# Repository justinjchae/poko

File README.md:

<div align="center">

# Poko

**A palm-sized, phone-free companion: the things you'd pick up your phone for, without picking up your phone.**

A round 240×240 display, one rotating ring, a haptic motor, a microphone and BLE to an iPhone app.
It snaps onto the back of the phone like a MagSafe accessory, or comes off and stands in for the phone at the gym, the library or on a walk.

`nRF52840` · `Zephyr / nRF Connect SDK` · `LVGL` · `BLE` · `MCUboot OTA` · `SwiftUI` · `Fusion 360 API` · `KiCad` · `JLCPCB`

<br>

&nbsp;

<sub>Left: the V1B prototype in hand, home ring on Voice Memos. Right: Pomodoro → workout logging → recording and browsing memos → Now Playing, all from the thumb wheel (2× speed).</sub>

</div>

---

## Contents

- [What it does](#what-it-does)
- [Requirements I've locked](#requirements-ive-locked)
- [System architecture](#system-architecture)
- [Hardware](#hardware)
- [Firmware](#firmware)
- [iPhone companion app](#iphone-companion-app)
- [Measured results](#measured-results)
- [Design direction](#design-direction)
- [Where it came from: Pokodoro (v0)](#where-it-came-from-pokodoro-v0)
- [Status and roadmap](#status-and-roadmap)
- [Repo map](#repo-map)
- [How this was built](#how-this-was-built)

---

## What it does

| | Use case | On the device | On the phone |
|---|---|---|---|
| ⏱ | **Pomodoro focus timer** | Ring sets the time, haptic ticks while turning, glanceable progress ring, silent vibration at the end | none |
| 🏋️ | **Workout tracker** | Today's exercises, the weight prefilled from last time with plates per side, rest timer, every set saved to flash | Routines are edited in the app and synced |
| 🎙 | **Voice memos** | Hold to record from any screen; ADPCM to on-board flash; works offline | Pulled over BLE, transcribed, titled and routed to Reminders, groceries or Calendar |
| 🎵 | Now Playing *(extra)* | Play/pause/skip and 16-step volume over Apple Media Service | none |
| ⌨️ | Desk keyboard *(extra)* | USB/BLE HID: ring as a scroll wheel, voice-to-typing | Transcription |

**What it won't do:** show notifications, run feeds, or ask you to scroll. One hand, eyes-free, every action confirmed by vibration.

---

## Requirements I've locked

These are the constraints every hardware and firmware decision is checked against. Full reasoning is in [`SPEC.md`](SPEC.md) and the part-by-part tracker [`docs/hardware/LOCK.md`](docs/hardware/LOCK.md).

### Product

| Requirement | Target |
|---|---|
| Form factor | MagSafe-style accessory, 60 × 90 mm outline, half-round top |
| Thickness | **8–9 mm** for production (the printed prototype is 18.8 mm; this is the hardest constraint) |
| Interaction | One hand, eyes-free. Turn moves focus, click commits; turning never silently changes a value |
| Navigation depth | Home → app → one detail level, max. Apps live at fixed clock positions on the home ring |
| Battery | Lasts a normal day; ~0.5 mA sleep-floor target |
| Offline | Device works without the phone; the phone does the heavy lifting (transcription, sync) |
| Manufacturing | Every part sourceable at ~100 units, JLC-assemblable, no injection mold for the first run |
| Prototyping rule | Internals must be printable (PLA/TPU) or stock commodity parts; dimensions tunable by reprint |
| Access rule | Every prototype breaks out spare GPIOs, 3V3/GND and an outside-reachable reset |

### Hardware decisions

| Subsystem | Decision | Why |
|---|---|---|
| MCU | **nRF52840**: XIAO Sense on a carrier board for the first batch, Raytac MDBT50Q module for production | BLE + battery life over the ESP32-S3 used in v0; the module is ~1.5–3 mm thinner and ~$6 cheaper than soldering down a dev board |
| Display | **1.28" round GC9A01 TFT**, 240×240, 4-wire SPI, bare 16-pin FPC panel | Round AMOLED was RFQ-only with ~1,000 MOQ; TFT has transparent low-volume pricing. Cost: the backlight dominates power, so it gets a discrete constant-current sink with PWM |
| Input | **Rotating ring + mechanical select**, AS5600 magnetic angle sensor on-axis | EC11 encoders are too thick for 8 mm. Optical, magnetic strip, inductive PCB coil and capacitive were weighed, and the press-sensing options were tested on rigs (see [Hardware](#hardware)) |
| Haptics | **LRA + DRV2605L**; detents simulated in software | One actuator gives detents, clicks and alerts with no mechanical detent to wear out or add thickness |
| Power | 500 mAh 303450 LiPo (3.0 mm thick), single-cell linear charger | Chosen to protect the thickness budget; battery life comes from backlight PWM and a low sleep floor |
| Storage | 16 MB QSPI NOR flash on the production board (memos + OTA slot), no SD card | About 31 minutes of memos alongside a full OTA image |
| Firmware | **Zephyr / nRF Connect SDK** | Real power management, MCUboot signed OTA, BLE stack. Arduino and CircuitPython were used only for bring-up |
| Enclosure | Machined shell (quote pending) with 3D-printed internals | Small batch; no mold until demand is proven |

---

## System architecture

```mermaid
flowchart LR
    subgraph Device["Poko (nRF52840, Zephyr)"]
        Ring["Ring<br/>AS5600 / EC11"] --> Input["Input + detent engine"]
        Btn["Select button"] --> Input
        IMU["6-axis IMU"] --> Pickup["Pickup-to-wake<br/>auto-rotate"]
        Mic["PDM mic"] --> Rec["Recorder<br/>ADPCM"]
        Input --> Shell["App shell<br/>home ring + apps"]
        Pickup --> Shell
        Shell --> UI["LVGL UI"] --> LCD["GC9A01 240×240"]
        Shell --> Haptic["Haptic patterns"] --> LRA["DRV2605L + LRA"]
        Rec --> Flash["Flash<br/>memo store"]
        Shell --> BLE["BLE<br/>GATT · AMS · HID · SMP"]
        Flash --> BLE
        OTA["MCUboot<br/>signed OTA"] -.-> Flash
    end

    subgraph Phone["iPhone companion (SwiftUI)"]
        Sync["Memo sync"] --> STT["On-device<br/>transcription"]
        STT --> Route["Voice-action router"]
        Route --> Rem["Reminders /<br/>groceries"]
        Route --> Cal["Google Calendar"]
        Routines["Workout routines"]
    end

    BLE <--> Sync
    BLE <--> Routines
```

---

## Hardware

### Prototype progression

| Stage | What | Status |
|---|---|---|
| **Breadboard bring-up** | XIAO nRF52840 Sense + round GC9A01 module + EC11 encoder (detent removed, shaft cut down) + ERM motor. CircuitPython first, then Zephyr | Done (Sept 2026) |
| **Enclosure V1B** | Two-part printed shell, 33 mm thumb wheel, display retainer, VHB-mounted XIAO, magnet in the back cover, support-free print orientations. 18.8 mm thick | Printed, carried daily to the gym and library |
| **Enclosure V2 (inset)** | Parametric Fusion 360 model driven from Python ([`cad/enclosure_v2_inset.py`](cad/enclosure_v2_inset.py)): 8 mm stack, datum-based [tolerance stack](docs/hardware/tolerance-stack.md), pairwise interference checks | Modelled |
| **Knob and ring test rigs** | Printed rigs + an ESP32-S3 logger streaming AS5600 angle/AGC/magnitude at 100 Hz to a Web Serial visualizer | Built and tested, see below |
| **XIAO carrier PCB** | Chin board carrying the display FPC, AS5600, DRV2605L/LRA, backlight sink, select-switch footprints | Next: floorplan → schematic → JLC order |

<table>
<tr>
<td align="center"><br><sub>V1B opened: cell, wiring, magnet in the back cover</sub></td>
<td align="center"><br><sub>Breadboard bring-up</sub></td>
<td align="center"><br><sub>Protoboard for the first enclosure</sub></td>
<td align="center"><br><sub>EC11 opened to remove the detent spring</sub></td>
<td align="center"><br><sub>Cutting the encoder shaft down</sub></td>
</tr>
</table>

### Ring input: what the rigs showed

The ring has to feel premium (the iPod click wheel is the reference) inside an 8 mm stack, so I built rigs and measured before committing:

- **Friction roller → AS5600:** worked, but felt overcomplicated and thin. Set aside.
- **Whole-knob press detected from magnet field strength (AS5600 AGC):** at a ~1 mm gap, rest AGC was 68–76 and a centre press dropped it to 32–37. A detector ("AGC drops ≥ 25 below the 3 s peak, held 150 ms, rotation < 4°") replayed 3/3 centre presses, 3/3 edge presses and 0 false triggers on turns.
- **Trackpad-style ring (≈0.05 mm travel, printed cantilever springs, 45° flare retention):** the thumb's grip while only rotating (AGC 24–35) overlapped edge presses (25–29). One sensor couldn't separate them reliably.
- **Decision:** AS5600 on-axis for rotation + a thin mechanical tact switch for select, with three switch footprints and spare I2C/GPIO on the carrier so the mechanism can change without a board respin.

Scripts: [`cad/as5600_knob_rig.py`](cad/as5600_knob_rig.py), [`cad/ring_rig.py`](cad/ring_rig.py), [`firmware/tools/as5600_rig/`](firmware/tools/as5600_rig) (logger firmware + visualizer).

### Electrical design notes

- **Backlight sink:** AO3400A + TLV9001 constant-current loop, 2.2 Ω sense, PWM-derived reference, op-amp powered from a GPIO so it draws nothing in sleep, gate pull-down for the unpowered state.
- **Charger swap check:** MCP73831 → TP4054. The check caught that the MCP73831's STAT pin drives ~4.6 V into a 3.0 V GPIO, and that the TP4054 PROG formula changes above 150 mA. Details in [`docs/hardware/LOCK.md`](docs/hardware/LOCK.md).
- **Pin budget:** all 11 XIAO pads allocated (SPI display, shared I2C for AS5600 + DRV2605L, select, backlight PWM/enable), one spare, with solder jumpers for optional lines ([`docs/hardware/pins.md`](docs/hardware/pins.md)).
- **Supply chain:** JLC quoted the Raytac module at **$15.69** vs. its own $7.73 list price and $6.50–7.13 at TME. At 100 units that gap is ~$840, so volume orders point to sourcing it elsewhere. Assembly-tier costs are in [`docs/hardware/jlc-cost.md`](docs/hardware/jlc-cost.md).

---

## Firmware

A Zephyr application split into a small OS layer and apps (source in a private repo; happy to walk through it):

- **`os/`**: input (EC11 Gray-code decoder, AS5600 driver), detent and haptic engine, LVGL screen and widgets, power states (dim, sleep, pickup-to-wake from the IMU), battery ADC, PDM capture with ADPCM, NVS-backed memo store, BLE link (custom GATT, Apple Media Service, HID keyboard), USB HID, MCUboot OTA, crash capture.
- **`apps/`**: Pomodoro, Gym (with synced routines), Voice memos, Now Playing, Desk keyboard, Settings.
- **Tooling:** a bench build that measures frame time, a power-test app for current measurements, a memo-pull script, and a desktop LVGL simulator.

Each feature was specced as a numbered brief with acceptance criteria and an outcome write-up.

---

## iPhone companion app

SwiftUI app (XcodeGen project, source in the same private repo): memo sync over BLE, on-device transcription, automatic titles, a voice-action router (to-dos, groceries, Google Calendar via OAuth PKCE), and workout routine editing. A routing eval harness scores the router against synthetic and real memo sets.

---

## Measured results

| What | Result | How |
|---|---|---|
| Current, screen off / on / recording | 37.5 / 42.6 / 44.0 mA | Multimeter in series with the battery, USB unplugged ([`power.md`](docs/hardware/power.md)) |
| Backlight share of screen-on draw | 33.5 mA (~79%) | Voltage across the module's 8.2 Ω backlight resistor. This is why the production board gets a PWM current sink |
| OTA over BLE | 561 KB in ~34 s, 42.5 s swap | MCUboot. A battery pull mid-swap recovered, and all 105 stored memos kept matching CRCs ([`ota-checks.md`](docs/hardware/ota-checks.md)) |
| Boot time | 53 s → **4.4 s** | Traced to a per-key NVS walk at boot, replaced with a single pass |
| Voice-to-text, release to typed | 5.9–6.3 s → ~3.0–3.7 s | Timing marks on device and phone, 5–7 s utterances |
| Voice-action routing accuracy | 47/54 → **52/54** on real memos | Eval harness, Apple on-device model |
| Album-art decode | 65 ms avg / 167 ms max | Measured, then cut: it made the UI lag |

---

## Design direction

<table>
<tr>
<td width="45%"></td>
<td>

**Inspiration:** concentric orbits on black, like the iOS Solar System lock screen. They map naturally onto a round display and a ring you turn.

- Black background, thin white line art, **one accent colour**
- Thick arc progress rings for timers
- Apps sit at fixed clock positions; only the focus moves, so you can go straight to one ("gym is at 2")
- Cheap pixels: small objects move over static, rotationally symmetric backgrounds, with no full-screen redraws
- Every turn and click confirmed by haptics, so it works without looking

</td>
</tr>
</table>

---

## Where it came from: Pokodoro (v0)

Poko is the second version of a device I started in 2024: **Pokodoro**, a portable Pomodoro timer that tells you a session is over with a vibration instead of a beep, so it works in a library or an office. I sketched it, prototyped it on protoboard, laid out a 4-layer board in KiCad, had it fabricated, hand-soldered it and designed the enclosure.

<table>
<tr>
<td align="center"><br><sub>Assembled v0</sub></td>
<td align="center"><br><sub>Custom PCB (KiCad 3D)</sub></td>
<td align="center"><br><sub>Inside the enclosure</sub></td>
</tr>
<tr>
<td align="center"><br><sub>UI sketches</sub></td>
<td align="center"><br><sub>Enclosure sketches</sub></td>
<td align="center"><br><sub>Protoboard MVP</sub></td>
</tr>
</table>

**Board:** ESP32-S3-WROOM-1, USB-C with a TVS ESD array, MCP73831 LiPo charger, Schottky OR-ing of USB and battery into a MIC5219 LDO, transistor-driven vibration motor and buzzer, SPI OLED header, two user buttons plus boot/reset. KiCad sources, Gerbers, BOM and placement files are in [`pokodoro/`](pokodoro/Pokodoro).

<details>
<summary>Schematic and copper layout</summary>
<br>

<br><br>

</details>

**What changed in Poko:** the MCU went to nRF52840 for BLE and battery life, a round colour display replaced the 128×64 OLED, a haptic ring replaced the buttons, the firmware moved to Zephyr with OTA and a phone app, and the scope grew from a timer into something to carry every day.

---

## Status and roadmap

**Current goal: a lendable batch of 7 units**, polished enough to hand to 3–5 people for two weeks of real use (Pomodoro, workouts, memos).

- [x] Firmware for all core apps running on the prototype, OTA proven
- [x] iPhone app: sync, transcription, routing, routines
- [x] Power measured, battery and backlight strategy set
- [x] Display, haptics and USB parts locked; samples ordered
- [x] Ring sensing decided after rig testing
- [ ] Mechanical select-switch jig (force vs. grip)
- [ ] XIAO carrier PCB: floorplan → schematic → layout → JLC assembly
- [ ] Enclosure V2 ring area rework, machining quote for 7
- [ ] Batch-1 build, lend, write up feedback
- [ ] Then: Raytac custom board, 100-unit quotes, preorder

---

## Repo map

```
SPEC.md                  concept, requirements, early BOM and power budget
docs/hardware/           part lock tracker, pins, power, haptics, OTA, tolerance stack, JLC cost
docs/images/             photos, demo GIF, KiCad exports
cad/                     parametric Fusion 360 scripts: enclosure, floorplan, test rigs, 3MF export
firmware/tools/as5600_rig/  ring-rig logger (ESP32-S3) + Web Serial visualizer and menu tests
pokodoro/                the v0 KiCad project (schematic, PCB, Gerbers, BOM)
```

Firmware (Zephyr, C) and the iPhone app (SwiftUI) are in a private repo and available on request.

---

## How this was built

I'm the sole developer. I set the requirements, made the hardware and part decisions, sourced parts and talked to suppliers, and built, printed and bench-tested every prototype and rig. Pokodoro (v0) I designed end to end myself. For Poko, most of the firmware, iOS and CAD-script code was written with AI coding agents (Claude Code) working from feature briefs. I wrote each brief's requirements, tested the results on real hardware, and accepted or rejected them.

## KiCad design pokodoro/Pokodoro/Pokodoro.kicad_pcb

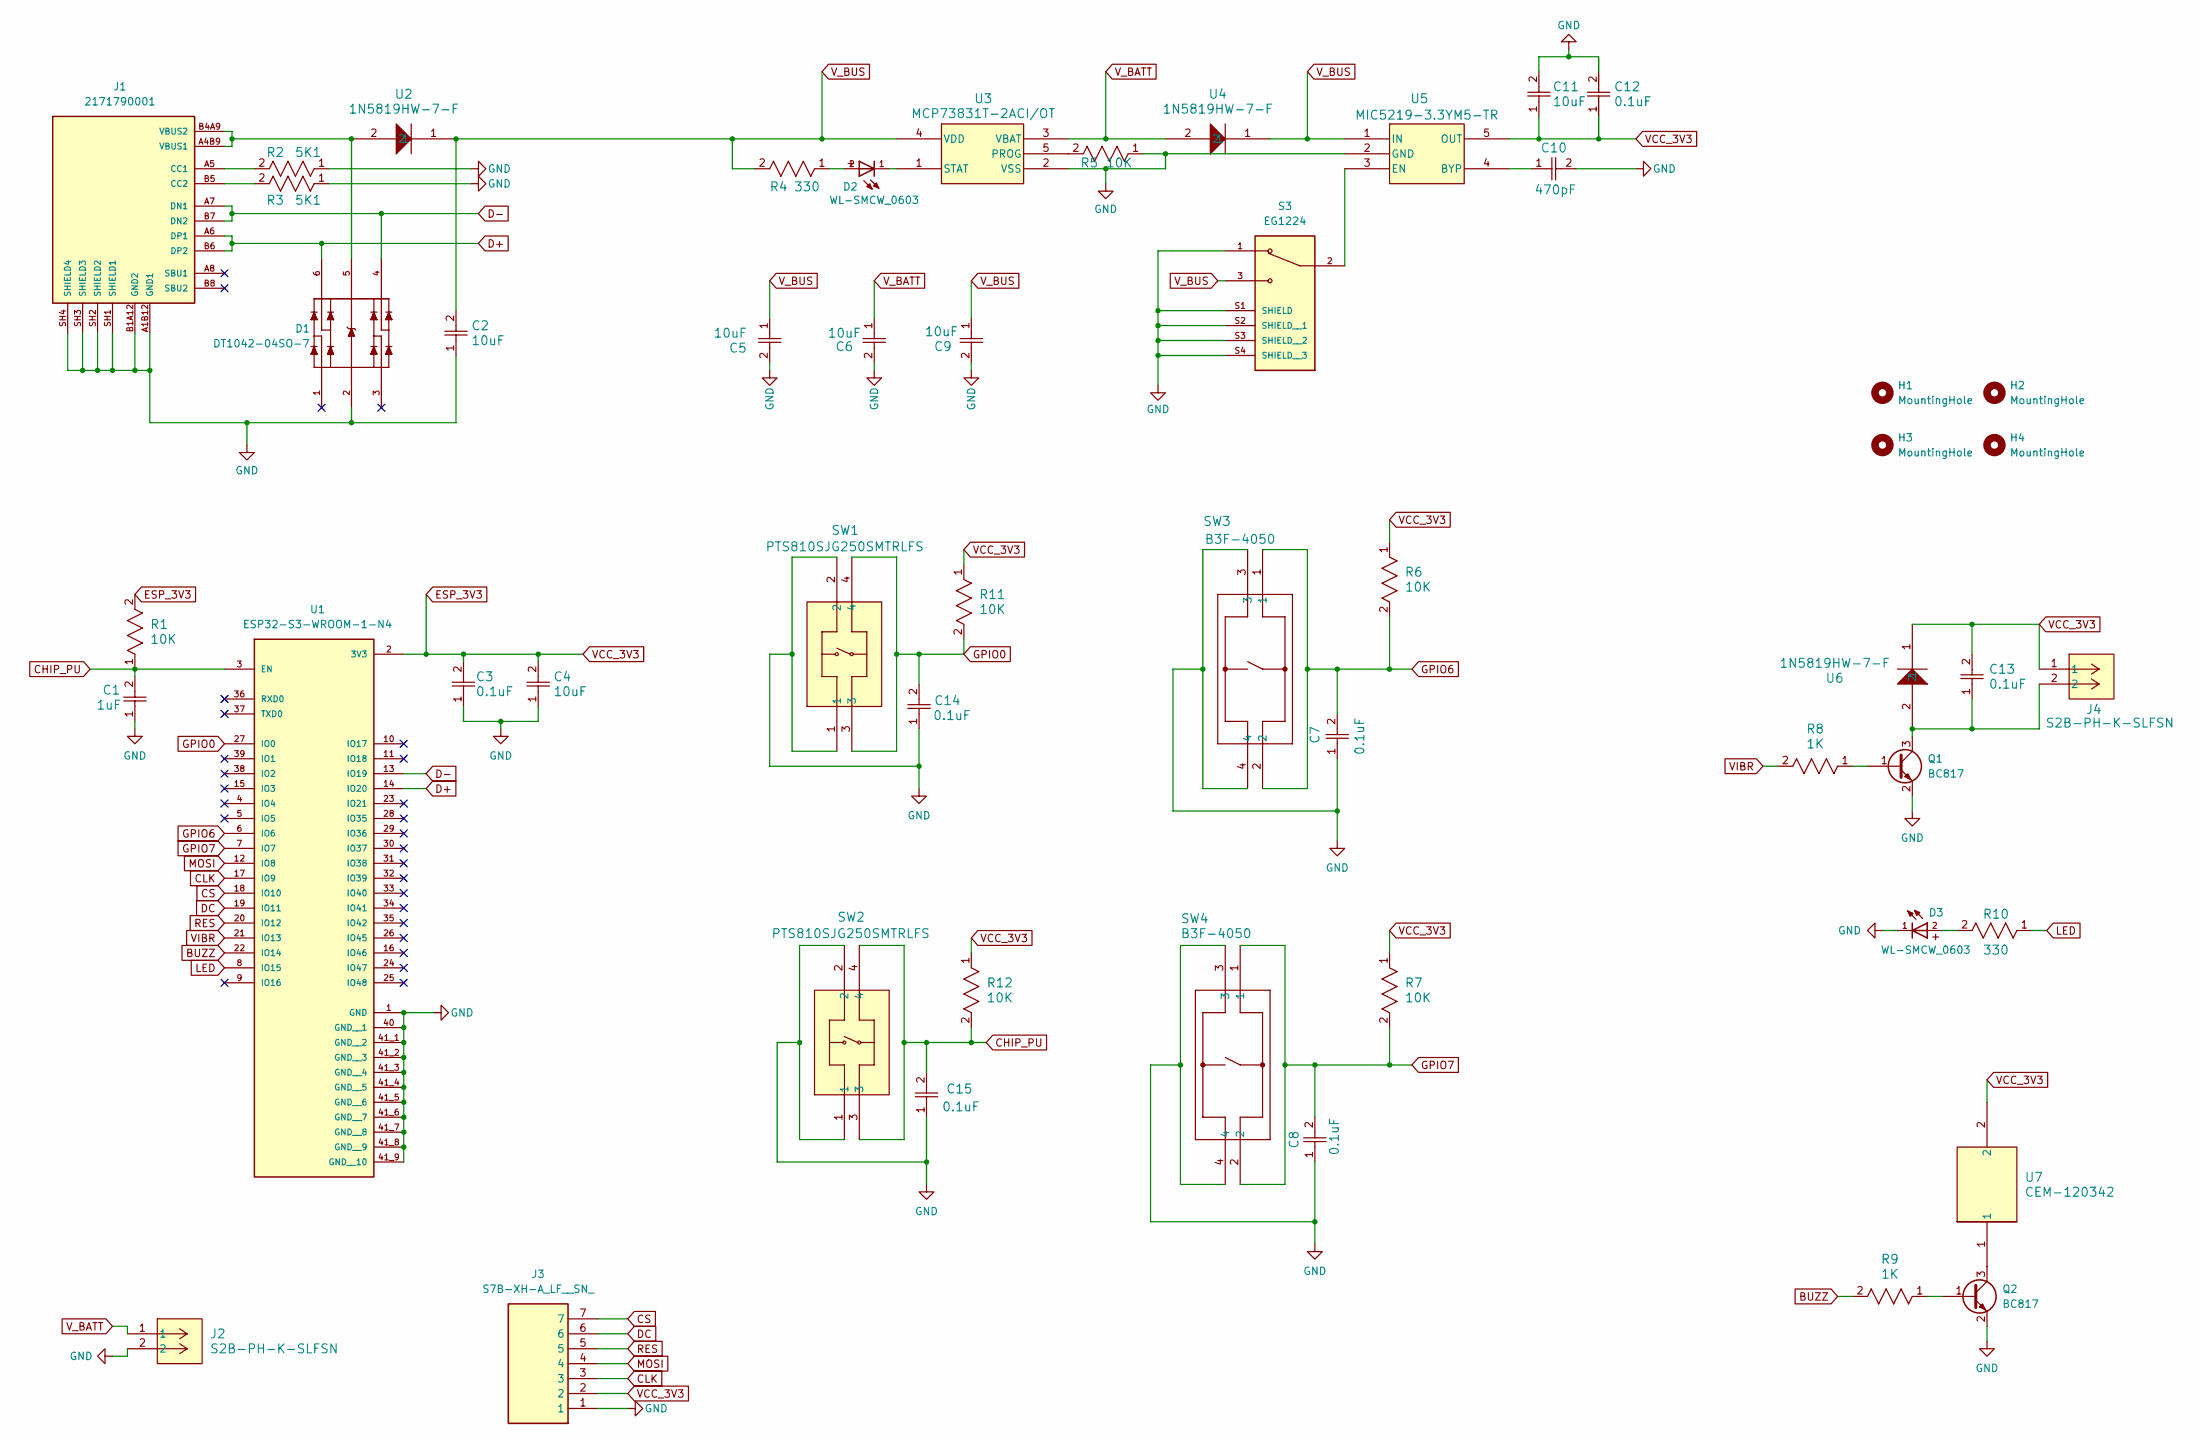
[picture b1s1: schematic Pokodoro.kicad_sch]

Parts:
C1: 1uF; CAP_CL10_SAM
C2, C4, C5, C6, C9, C11: 10uF; CAP_CL10_SAM
C3, C7, C8, C12, C13, C14, C15: 0.1uF; CAP_CL10_SAM
C10: 470pF; G-188_MUR
D1: DT1042-04SO-7; DT1042-04SO; PARTREV 2-2; DigiKey_Part_Number DT1042-04SO-7DITR-ND
D2, D3: WL-SMCW_0603
H1, H2, H3, H4: MountingHole; MountingHole_3.2mm_M3
J1: 2171790001; USBC_MOLEX_2171790001; PARTREV A1
J2, J4: S2B-PH-K-SLFSN; S2B-PH-K-S
J3: S7B-XH-A_LF__SN_; S7B-XH-A-1; Mouser Part Number 306-S7B-XH-ALFSN
Q1, Q2: BC817; BC817-40
R1, R5, R6, R7, R11, R12: 10K; RC0603N_YAG
R2, R3: 5K1; RC0603N_YAG
R4, R10: 330; RC0603N_YAG
R8, R9: 1K; RC0603N_YAG
S3: EG1224; PARTREV A
SW1, SW2: PTS810SJG250SMTRLFS; PTS810
SW3, SW4: B3F-4050
U1: ESP32-S3-WROOM-1-N4; PARTREV v1.0
U2, U4, U6: 1N5819HW-7-F; 1N5819HW-7-F_DIO
U3: MCP73831T-2ACI/OT; SOT-23-5_MC_MCH
U5: MIC5219-3.3YM5-TR; SOT-23-5_M5_MCH
U7: CEM-120342

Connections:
BUZZ: R9.2, U1.22 (IO14)
CHIP_PU: C1.2, C15.2, R1.1, R12.2, SW2.3, SW2.4, U1.3 (EN)
CLK: J3.3, U1.17 (IO9)
CS: J3.7, U1.18 (IO10)
D+: D1.6, J1.A6 (DP1), J1.B6 (DP2), U1.14 (IO20)
D-: D1.4, J1.A7 (DN1), J1.B7 (DN2), U1.13 (IO19)
DC: J3.6, U1.19 (IO11)
ESP_3V3: C3.2, C4.2, C11.1, C12.1, C13.2, J3.2, J4.1, R1.2, R6.1, R7.1, R11.1, R12.1, U1.2 (3V3), U5.5 (OUT), U6.1, U7.2
GND: C1.1, C2.1, C3.1, C4.1, C5.2, C6.2, C7.1, C8.1, C9.2, C10.2, C11.2, C12.2, C14.1, C15.1, D1.2, D3.1, J1.A1B12 (GND1), J1.B1A12 (GND2), J1.SH1 (SHIELD1), J1.SH2 (SHIELD2), J1.SH3 (SHIELD3), J1.SH4 (SHIELD4), J2.2, J3.1, Q1.2 (E), Q2.2 (E), R2.1, R3.1, R5.1, S3.1, S3.S1 (SHIELD), S3.S2 (SHIELD__1), S3.S3 (SHIELD__2), S3.S4 (SHIELD__3), SW1.1, SW1.2, SW2.1, SW2.2, SW3.3, SW3.4, SW4.3, SW4.4, U1.1 (GND), U1.40 (GND__1), U1.41_1 (GND__2), U1.41_2 (GND__3), U1.41_3 (GND__4), U1.41_4 (GND__5), U1.41_5 (GND__6), U1.41_6 (GND__7), U1.41_7 (GND__8), U1.41_8 (GND__9), U1.41_9 (GND__10), U1.41_10, U1.41_11, U1.41_12, U1.41_13, U1.41_14, U1.41_15, U1.41_16, U1.41_17, U1.41_18, U1.41_19, U1.41_20, U1.41_21, U3.2 (VSS), U5.2 (GND)
GPIO0: C14.2, R11.2, SW1.3, SW1.4, U1.27 (IO0)
GPIO6: C7.2, R6.2, SW3.1, SW3.2, U1.6 (IO6)
GPIO7: C8.2, R7.2, SW4.1, SW4.2, U1.7 (IO7)
LED: R10.1, U1.8 (IO15)
MOSI: J3.4, U1.12 (IO8)
unnamed: D2.2, R4.1
unnamed: D3.2, R10.2
unnamed: J1.A5 (CC1), R2.2
unnamed: J1.B5 (CC2), R3.2
unnamed: D1.5, J1.A4B9 (VBUS1), J1.B4A9 (VBUS2), U2.2
unnamed: Q1.1 (B), R8.1
unnamed: C13.1, J4.2, Q1.3 (C), U6.2
unnamed: Q2.1 (B), R9.1
unnamed: Q2.3 (C), U7.1
unnamed: R5.2, U3.5 (PROG)
unnamed: D2.1, U3.1 (STAT)
unnamed: C10.1, U5.4 (BYP)
unnamed: S3.2, U5.3 (EN)
RES: J3.5, U1.20 (IO12)
VIBR: R8.2, U1.21 (IO13)
V_BATT: C6.1, J2.1, U3.3 (VBAT), U4.2
V_BUS: C2.2, C5.1, C9.1, R4.2, S3.3, U2.1, U3.4 (VDD), U4.1, U5.1 (IN)

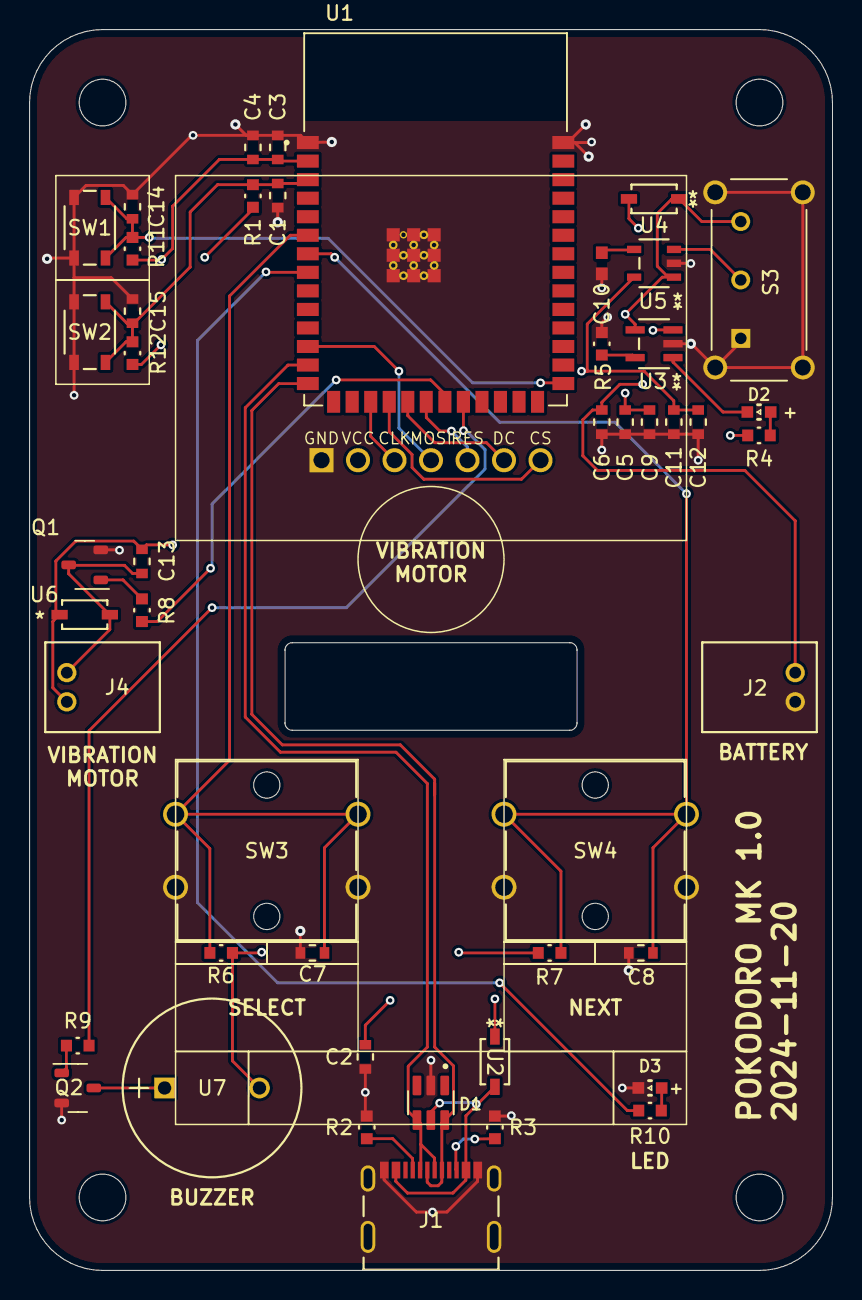
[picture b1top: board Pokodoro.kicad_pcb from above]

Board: 4 copper layers, 55.0 x 85.0 mm, 52 parts (1 on the bottom side), 31 nets.
